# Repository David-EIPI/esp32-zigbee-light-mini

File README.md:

# esp32-zigbee-light-mini

Compact version of the remotely controlled indoor light based on ESP32-H2 and Home Assistant.

## Overview

This is a compact version of the [esp32-zigbee-light](https://github.com/David-EIPI/esp32-zigbee-light "Remotely controlled indoor light powered by ESP32-H2"), small enough to fit into an in-ceiling electrical box, enabling neat conversion of a standard ceiling fixture into a smart light.

This project utilizes a compact WROOM-03 module with an edge connector. The overall design follows [esp32-zigbee-light](https://github.com/David-EIPI/esp32-zigbee-light "Remotely controlled indoor light powered by ESP32-H2").

## Firmware

The firmware is written in C and built with `idf.py`. It implements a zero-crossing detector for TRIAC-based dimming and supports the **HLK-LD2420S** mmWave motion sensor with adjustable sensing distance. The firmware exposes 7 endpoints and 13 clusters:

* **6 Analog Output clusters** (configuration)
* **2 Analog Input clusters** (presence detection distance, calibration control)
* **2 Binary Input clusters** (motion state, light state)
* **1 Multistate Value cluster** (operation mode)
* **1 OnOff cluster** (dimming enable control)
* **1 Temperature cluster** (MCU internal temperature)

This design includes an additional temperature cluster due to the compact, enclosed setup. Monitoring internal temperature becomes important in this system.

See [here](https://github.com/David-EIPI/esp32-zigbee-light/blob/main/BUILD.md) instructions on building the firmware using `idf.py` on Linux.

### Sensor calibration

In this compact design, the LD2420s motion sensor has shown somewhat unstable output. Even without any motion, it occasionally "detects" activity at random distances. This likely results from EMI generated by the power supply, the microcontroller core, or the radio. Fortunately, the LD2420s sensor supports programmable signal thresholds, allowing for in-place calibration. The calibration approach and initial code are based on the [ESPHome LD2420 plugin](https://github.com/esphome/esphome/blob/dev/esphome/components/ld2420 "ESPHome LD2420 plugin").

Calibration is initiated by writing a numerical value (interpreted as calibration duration in seconds) to the Analog Input cluster at Endpoint 2. A ZHA quirk can provide a button to conveniently start calibration.

## Hardware

Schematics and PCB layout were created using KiCad. The board integrates an AC-DC power supply, ESP32-H2 controller, LD2420s sensor, TRIAC, and associated control circuitry. Input protection includes a current fuse, thermal fuse, and a TVS diode. The TRIAC control circuit matches the one in [esp32-zigbee-light](https://github.com/David-EIPI/esp32-zigbee-light "Remotely controlled indoor light powered by ESP32-H2").

### Power supply

The largest component on the board is the AC-DC converter.

This is the HLK-2M03 from HiLink, an isolated 3.3 V, 600 mA converter.  Measured ESP32 consumption is approximately 20 mA during RF transmission, and the documented LD2420s consumption averages around 50 mA, with occasional peaks of about 70 mA. Including the optocoupler current, total demand should not exceed 100 mA. HLK-2M03 is somewhat oversized for this design but smaller modules appear unavailable.

### ESP32-H2 Wroom-03 module

The module is designed for vertical mounting to conserve PCB space. Its height above the board is 16 mm, which is lower than the AC-DC module, thus not affecting the overall dimensions.

Soldering this module presented some challenges:

First, the slot recommended by the datasheet is excessively wide, causing the module to fit loosely and leaving large air gaps difficult to bridge with solder. To resolve this, I soldered short wire segments to the pads as guides, but the result still looks ugly. I wonder if wave soldering would work for this module.

Second, programming is performed via small test pads (USB or serial port). In the datasheet I did not find any recommendations regarding manufacturer-supported programming fixtures. While some users create custom 3D-printed jigs, I opted to solder free-hanging wires directly to the module’s USB pads, enabling programming and debugging after board assembly.

### Enclosure

The PCB was designed to fit one of the many enclosures sold on AliExpress. Many sellers offer identical boxes; I purchased this one below:

The assembled board fits almost perfectly, though slight filing was necessary on the cutouts made for the mounting posts. The inner height of the enclosure just accommodates the AC-DC converter, leaving insufficient room to place the board on top of the mounting posts. Instead, I made small cutouts around the posts, allowing the board to sit flat at the bottom.

To ensure proper fit, the board's bottom side needed to remain completely flat. The AC-DC converter’s leads were trimmed flush, and minimal solder was used to avoid bulges. All other through-hole components were soldered from the top side while pressing the board firmly onto a flat surface, which is why they “hover” above the board surface.

The enclosure features convenient side-wall cutouts for wiring; however, matching cutouts on the lid’s inner rim were missing and had to be manually added. Below is the final assembled enclosure, shown alongside a CR2032 battery for scale reference:

## ZHA Quirk

The ZHA quirk supporting this device is essentially identical to that in the [esp32-zigbee-light](https://github.com/David-EIPI/esp32-zigbee-light "Remotely controlled indoor light powered by ESP32-H2") project, with only minor additions required to enable sensor calibration requests. This functionality can be implemented in two ways:

* Using the `.number()` method, which defaults to a CONFIG entity displayed as a slider. Setting this slider triggers calibration for the selected duration.
* Using the `.write_attr_butt()` method, creating a button that sets a predefined attribute value upon pressing.

I have left both methods are in the quirk file for reference.

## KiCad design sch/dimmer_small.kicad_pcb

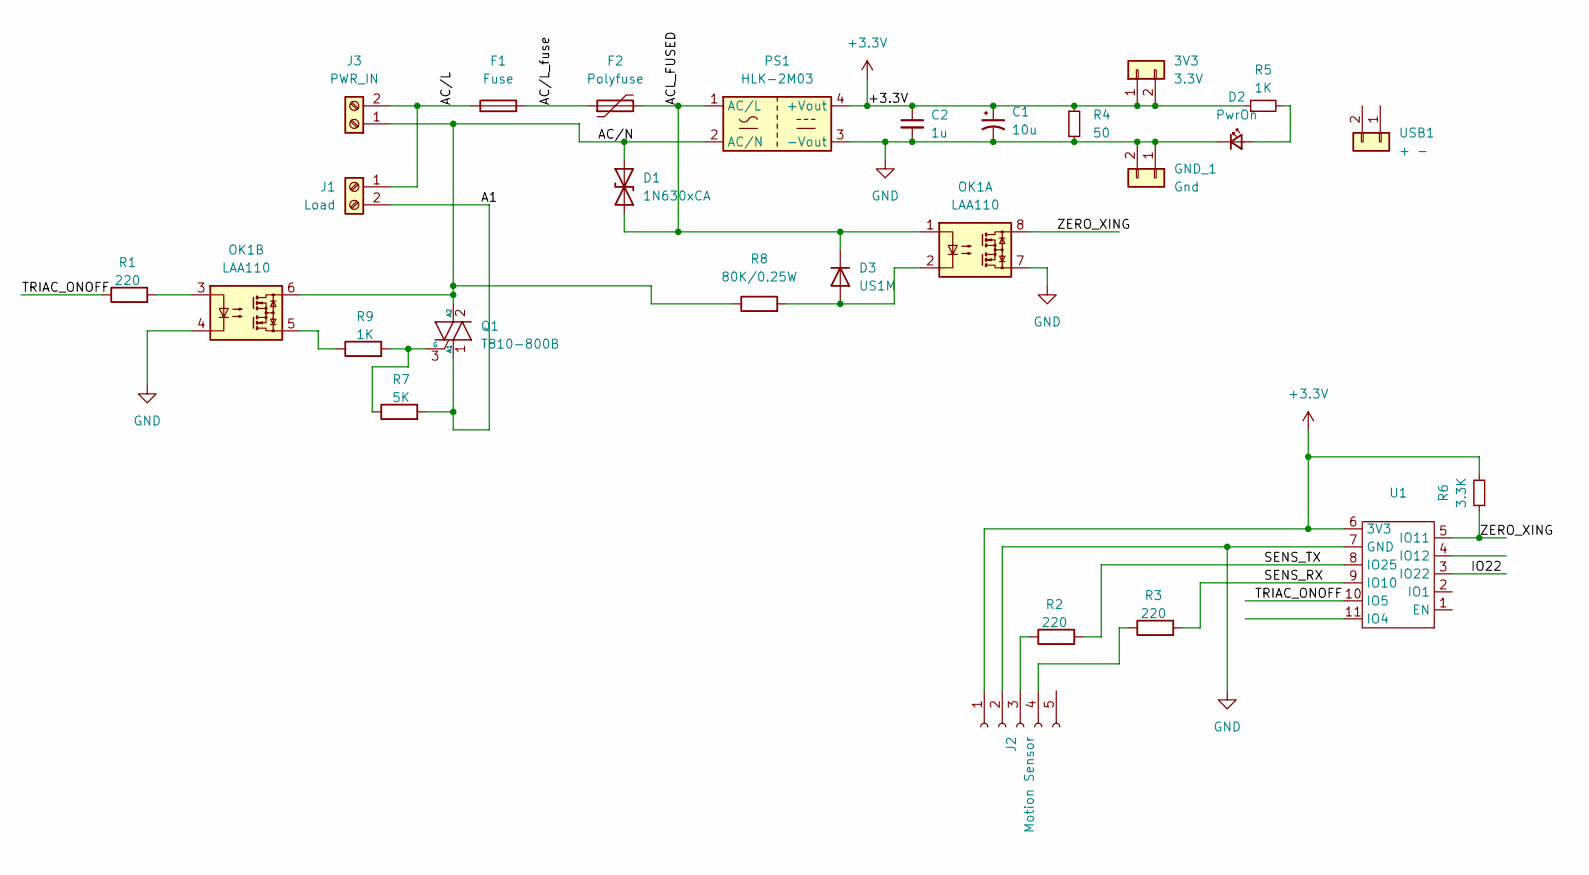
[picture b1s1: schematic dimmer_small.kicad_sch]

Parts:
3V3: 3.3V; PinHeader_1x02_P2.54mm_Vertical
C1: 10u; CP_Radial_D5.0mm_P2.50mm
C2: 1u; C_0805_2012Metric_Pad1.18x1.45mm_HandSolder
D1: 1N630xCA; PinHeader_2x01_P2.54mm_Vertical
D2: PwrOn; LED_0603_1608Metric_Pad1.05x0.95mm_HandSolder
D3: US1M; Nexperia_CFP3_SOD-123W
F1: Fuse; Fuse_1206_3216Metric_Pad1.42x1.75mm_HandSolder
F2: Polyfuse; Fuse_Bourns_MF-RHT1000
GND_1: Gnd; PinHeader_1x02_P2.54mm_Vertical
J1: Load; Fuse_1210_3225Metric
J2: Motion Sensor; PinHeader_1x05_P2.54mm_Vertical
J3: PWR_IN; Fuse_1210_3225Metric
OK1: LAA110; DIP-8_W7.62mm
PS1: HLK-2M03; Converter_ACDC_Hi-Link_HLK-2Mxx
Q1: T810-800B; TO-252-2
R1, R2, R3: 220; R_0603_1608Metric_Pad0.98x0.95mm_HandSolder
R4: 50; R_0805_2012Metric_Pad1.20x1.40mm_HandSolder
R5: 1K; R_0603_1608Metric_Pad0.98x0.95mm_HandSolder
R6: 3.3K; R_0603_1608Metric_Pad0.98x0.95mm_HandSolder
R7: 5K; R_1206_3216Metric_Pad1.30x1.75mm_HandSolder
R8: 80K/0.25W; R_1206_3216Metric_Pad1.30x1.75mm_HandSolder
R9: 1K; R_1206_3216Metric_Pad1.30x1.75mm_HandSolder
U1: ESP32-H2-WROOM-03
USB1: + -; PinHeader_1x02_P2.54mm_Vertical

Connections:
+3.3V: 3V3.1, 3V3.2, C1.1, C2.1, J2.1, PS1.4 (+Vout), R4.1, R5.1, R6.2, U1.6 (3V3)
/A1: J1.2, Q1.1 (A1), R7.2
/ACL_FUSED: D1.1 (A1), D3.1 (K), F2.2, OK1.1, PS1.1 (AC/L)
/AC/L: F1.1, J1.1, J3.2
/AC/L_fuse: F1.2, F2.1
/AC/N: D1.2 (A2), J3.1, OK1.6, PS1.2 (AC/N), Q1.2 (A2), R8.1
/IO22: U1.3 (IO22)
/SENS_RX: R3.2, U1.9 (IO10)
/SENS_TX: R2.2, U1.8 (IO25)
/TRIAC_ONOFF: R1.1, U1.10 (IO5)
/ZERO_XING: OK1.8, R6.1, U1.5 (IO11)
GND: C1.2, C2.2, D2.1 (K), GND_1.1, GND_1.2, J2.2, OK1.4, OK1.7, PS1.3 (-Vout), R4.2, U1.7 (GND)
unnamed: D2.2 (A), R5.2
unnamed: D3.2 (A), OK1.2, R8.2
unnamed: J2.3, R2.1
unnamed: J2.4, R3.1
unnamed: OK1.3, R1.2
unnamed: OK1.5, R9.1
unnamed: Q1.3 (G), R7.1, R9.2

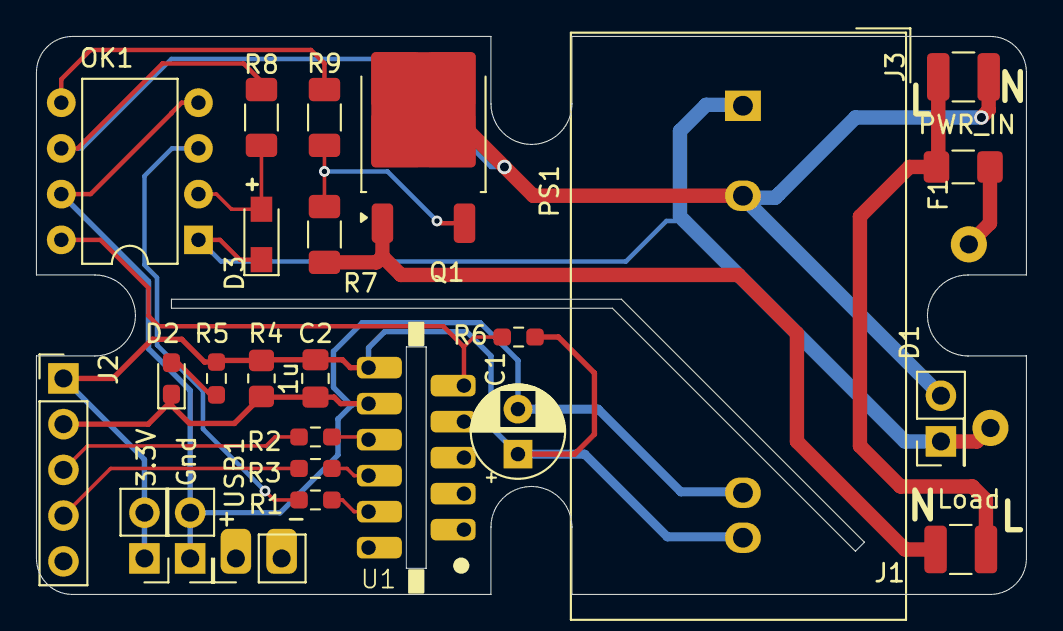
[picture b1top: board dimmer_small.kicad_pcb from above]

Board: 2 copper layers, 55.0 x 31.0 mm, 26 parts (1 on the bottom side), 18 nets.

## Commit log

2025-05-10 Initial upload.
2025-05-10 Added schematics and PCB
2025-06-21 Remove reference to const.UNITS since zigpy now implements BACNet units.
2025-07-29 Move firmware files into own folder
2025-07-29 Add link to the build instructions
2025-07-29 Add gitignore
2025-07-29 Fix the link to the build instructions
